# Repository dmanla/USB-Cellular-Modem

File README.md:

# USB-Cellular-Modem: NB-IoT/Cat-M Terminal

## Overview
**USB-Cellular-Modem** is an open-hardware cellular terminal designed for to enable any device equipped with USB to interface with LTE-CAT-M1 or NB-IOT Cellular Networks. The modem is low-power enough to be used as a back-up cellular interface for any mobile device. 

**NOTE:** Due to Apple restrictions on USB Interface access, this device cannot interface with Apple Devices. There may be a bluetooth variant in the future.

The core of the device is the **SIMCOM 7080G**, providing global NB-IoT and Cat-M1 connectivity with a focus on a minimal RF footprint and user-controlled privacy.

---

## Key Security & Design Features
* **Active-Discharge Kill Switch**: A physical SPDT slide switch ($SW1$) that disconnects the buck converter and actively shorts the $+BATT$ rail to ground through a $10\Omega$ resistor ($R4$). This ensures the $1000\mu F$ bulk capacitance is drained in milliseconds, preventing any residual "heartbeat" transmissions.
* **UART Signal Isolation**: $1k\Omega$ series resistors ($R8$, $R9$, $R10$, $R11$) are placed on all data lines (TX, RX, RTS, DTR). This prevents the **CH343P** from "back-powering" the modem via internal ESD diodes when the master power is cut.
* **Automated Power Trigger**: The **DTR** line is tied to a **DTC143Z** digital transistor ($Q1$). Opening the serial port on the host machine automatically pulses the modem's **PWRKEY**, initiating the boot sequence.
* **Local RF Shielding**: The PCB includes grounded rectangular frames designed for soldering a metal Faraday cage over the antenna matching network ($J1$, $C2$, $R1$, $C3$) to mitigate local signal sniffing.
* **eSIM Integration**: Includes a dedicated footprint for the **ST4SIM-200M** GSMA-certified eSIM for tamper-resistant credential storage.

---

### Included Hardware
| Component | Part Number | Description |
| :--- | :--- | :--- |
| **Cellular Module** | **SIMCOM 7080G** | Global NB-IoT / Cat-M1 with GNSS. |
| **USB-UART Bridge** | **WCH CH343P** | High-speed USB to serial converter. |
| **Power Regulator** | **TPS62A01ADRL** | 1000mA Synchronous Buck Converter (5V to 3.8V). |
| **Embedded SIM** | **ST4SIM-200M** | Industrial-grade MFF2 eSIM. |
| **Nano SIM Slot** | **CUI Hinged NSIM-2** | Nano-SIM Card Slot. |

---

## Technical Specifications
* **Input Power**: USB VBUS (+5V, 500mA).
* **Logic Level**: $1.8V$ Internal ($VDD\_EXT$), isolated from $3.3V$ USB signals.
* **Stackup**: 4-Layer PCB with solid internal ground planes.
* **EDA Software**: **KiCad 9.0.7**.

## Usage
1.  **Enable Device**: Flip $SW1$ to the `ON` position.
2.  **Communication**: Open a serial terminal (e.g., `minicom` or `screen`) at `115200` baud. The DTR toggle will boot the modem.
3.  **Kill Session**: Flip $SW1$ to the `OFF` position. The modem is physically disconnected and the power rail is grounded.

---

## Front 3D Render

## Back 3D Render

## License

Dimensions and Modem Placement Derived from [techstudio-design/sim7080_dev_board](https://github.com/techstudio-design/sim7080_dev_board)

All PCB design files and hardware are released under the [Creative Commons Attribution Share Alike 4.0](https://choosealicense.com/licenses/cc-by-sa-4.0/) license.

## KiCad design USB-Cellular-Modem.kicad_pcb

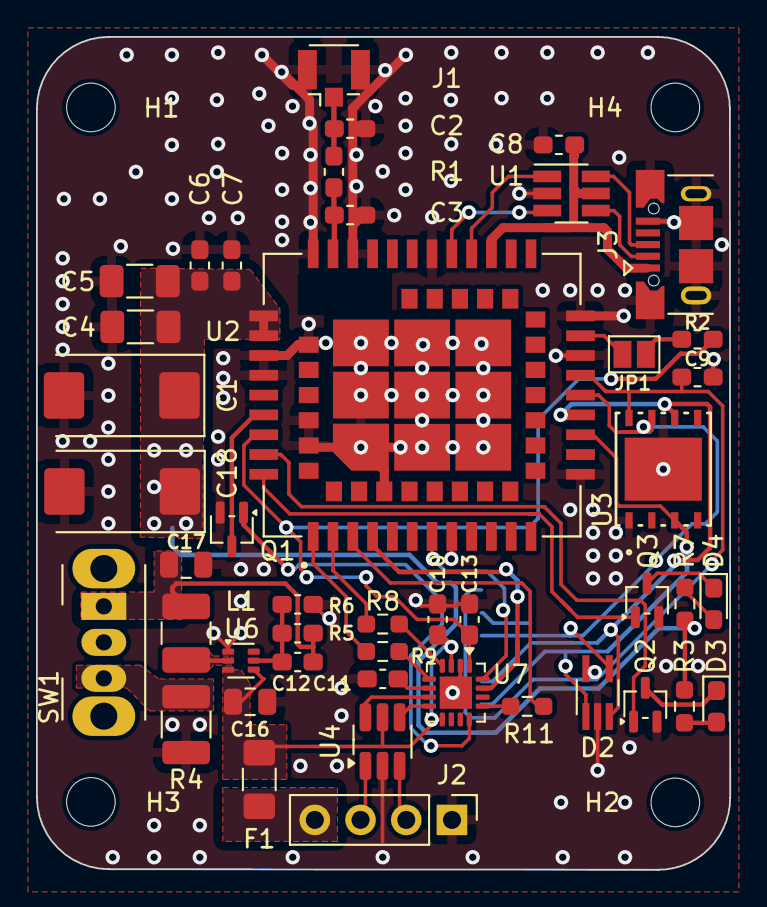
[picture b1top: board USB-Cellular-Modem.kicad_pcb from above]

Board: 4 copper layers, 38.5 x 46.3 mm, 50 parts (1 on the bottom side), 43 nets.

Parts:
C1, C18: 500uF; CP_EIA-7343-30_AVX-N_HandSolder
C2, C3: NC; C_0603_1608Metric_Pad1.05x0.95mm_HandSolder
C4, C5: 100uF; C_1206_3216Metric_Pad1.33x1.80mm_HandSolder
C6: 1uF; C_0603_1608Metric_Pad1.05x0.95mm_HandSolder
C7, C8, C9: 0.1uF; C_0603_1608Metric_Pad1.05x0.95mm_HandSolder
C10, C13: 1uF; C_0603_1608Metric_Pad1.08x0.95mm_HandSolder
C11: 100nF; C_0603_1608Metric_Pad1.08x0.95mm_HandSolder
C12: 120pF; C_0603_1608Metric_Pad1.08x0.95mm_HandSolder
C16: 10uF; C_0805_2012Metric
C17: 22uF; C_0805_2012Metric
D2: ESDA6V1W5; SOT-353_SC-70-5_Handsoldering
D3: NETLIGHT; LED_0603_1608Metric_Pad1.05x0.95mm_HandSolder
D4: STATUS; LED_0603_1608Metric_Pad1.05x0.95mm_HandSolder
F1: PTC_FUSE; Fuse_1206_3216Metric_Pad1.42x1.75mm_HandSolder
H1, H2, H3, H4: MountingHole_Pad; MountingHole_2.7mm_M2.5
J1: LTE Antenna; U.FL_Hirose_U.FL-R-SMT-1_Vertical
J2: USB_JUMPER; PinHeader_1x04_P2.54mm_Vertical
J3: USB_B_Micro; USB_Micro-B_XKB_U254-051T-4BH83-F1S
J4: SIM_Card; nanoSIM_Hinged_CUI_NSIM-2-C
JP1: SolderJumper_2_Open; SolderJumper-2_P1.3mm_Open_Pad1.0x1.5mm
L1: 1uH; L_1210_3225Metric_Pad1.42x2.65mm_HandSolder
Q1: DTC143Z; SOT-323_SC-70
Q2, Q3: DTC143ZU; SOT-323_SC-70
R1: 0; R_0603_1608Metric_Pad1.05x0.95mm_HandSolder
R2: 10k; R_0603_1608Metric_Pad1.05x0.95mm_HandSolder
R3, R7, R8, R9, R11: 1k; R_0603_1608Metric_Pad0.98x0.95mm_HandSolder
R4: 10R; R_1210_3225Metric_Pad1.30x2.65mm_HandSolder
R5: 536k; C_0603_1608Metric_Pad1.08x0.95mm_HandSolder
R6: 100k; C_0603_1608Metric_Pad1.08x0.95mm_HandSolder
SW1: KILL_SWITCH; SW_Slide_SPDT_Angled_CK_OS102011MA1Q
U1, U4: USBLC6-2SC6; SOT-23-6_Handsoldering
U2: SIM7080G
U3: ST4SIM-200M
U6: TPS62A01ADRL; SOT-563
U7: CH343P; WCH_QFN-16-1EP_3x3mm_P0.5mm_EP1.8x1.8mm

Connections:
+1V8: C13.1, R2.1, U2.40 (VDD_EXT), U7.1 (VIO)
+5V: C10.1, C16.1, F1.2, U4.5 (VBUS), U6.3 (VIN), U6.4 (EN), U7.3 (VDD5), U7.9 (VBUS)
+BATT: C1.1, C4.1, C5.1, C6.1, C7.1, C18.1, R3.1, R7.1, SW1.2 (B), U2.34 (VBAT), U2.35 (VBAT)
/SIM7080_Interface/PWR_SIGNAL: Q1.3 (C), U2.39 (PWRKEY)
/SIM7080_Interface/UART_RXD: R9.2, U2.1 (UART1_TXD)
/SIM7080_Interface/UART_TXD: R8.2, U2.2 (UART1_RXD)
/SIM7080_Interface/UART_~CTS: U2.4 (UART1_CTS), U7.15 (~CTS)
/SIM7080_Interface/UART_~RI: U2.7 (UART1_RI), U7.16 (~RI)
/SIM7080_Interface/UART_~RTS: R11.2, U2.3 (UART1_RTS)
/SIM7080_module/DEBUG_VBUS: C8.1, J3.1 (VBUS), U1.5 (VBUS), U2.24 (USB_VBUS)
/SIM7080_module/NET_LED_CTRL: Q2.1 (B), U2.41 (NETLIGHT)
/SIM7080_module/STATUS_LED_CTRL: Q3.1 (B), U2.42 (STATUS)
GND: C1.2, C2.2, C3.2, C4.2, C5.2, C6.2, C7.2, C8.2, C9.2, C10.2, C11.2, C13.2, C16.2, C17.2, C18.2, D2.2 (A), J1.2 (Ext), J2.1, J3.5 (GND), J3.6 (Shield), J4.5 (GND), Q1.2 (E), Q2.2 (E), Q3.2 (E), R4.2, R6.2, U1.2 (GND), U2.8 (GND), U2.13 (GND), U2.19 (GND), U2.21 (GND), U2.27 (GND), U2.30 (GND), U2.31 (GND), U2.33 (GND), U2.36 (GND), U2.37 (GND), U2.45 (GND), U2.63 (GND), U2.66 (GND), U2.67 (GND), U2.69 (GND), U2.70 (GND), U2.71 (GND), U2.72 (GND), U2.73 (GND), U2.74 (GND), U2.75 (GND), U2.76 (GND), U2.77 (GND), U3.1 (GND), U3.9, U4.2 (GND), U6.1 (GND), U7.2 (GND), U7.17 (GND_EPAD)
unnamed: D3.2 (A), R3.2
unnamed: D3.1 (K), Q2.3 (C)
unnamed: D4.2 (A), R7.2
unnamed: D4.1 (K), Q3.3 (C)
unnamed: C2.1, J1.1 (In), R1.2
unnamed: J2.2, U4.3 (IO2)
unnamed: J2.3, U4.1 (IO1)
unnamed: J3.3 (D+), U1.6 (IO1)
unnamed: J3.2 (D-), U1.4 (IO2)
unnamed: D2.3 (K), J4.3 (CLK), U2.16 (SIM_CLK), U3.6 (CLK)
unnamed: D2.1 (K), J4.7 (I/O), U2.15 (SIM_DATA), U3.3 (I/O)
unnamed: D2.4 (K), J4.2 (RST), U2.17 (SIM_RST), U3.7 (RESET)
unnamed: C9.1, D2.5 (K), J4.1 (VCC), U2.18 (SIM_VDD), U3.8 (VCC)
unnamed: JP1.1 (A), U2.20 (BOOT_CFG)
unnamed: JP1.2 (B), R2.2
unnamed: Q1.1 (B), U7.12 (~DTR)
unnamed: C12.1, C17.1, L1.2, R5.1, SW1.1 (A)
unnamed: R4.1, SW1.3 (C)
unnamed: C3.1, R1.1, U2.32 (RF_ANT)
unnamed: U1.3 (IO2), U2.26 (USB_DM)
unnamed: U1.1 (IO1), U2.25 (USB_DP)
unnamed: C12.2, R5.2, R6.1, U6.5 (FB)
unnamed: L1.1, U6.2 (SW)
unnamed: R9.1, U7.5 (RXD)
unnamed: R8.1, U7.4 (TXD)
unnamed: U4.6 (IO1), U7.7 (UD+)
unnamed: U4.4 (IO2), U7.8 (UD-)
unnamed: C11.1, U7.6 (V3_{OUT})
unnamed: R11.1, U7.13 (~RTS)
VBUS: F1.1, J2.4

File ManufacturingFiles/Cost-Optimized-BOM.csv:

Reference,Qty,Value/Description,Manufacturer,Part Number,Distributor,Unit Price (10 Qty),Total (10 Qty)
U2,1,Cellular Module Cat-M/NB-IoT,SimCom,SIM7080G,LCSC (C2943992),$10.86,$108.60
U3,1,eSIM IC GSMA,STMicroelectronics,ST4SIM-200M,Mouser / ST,$3.00,$30.00
U7,1,USB to UART Bridge,WCH,CH343P,LCSC (C2846043),$1.03,$10.30
U6,1,Buck Converter 1A,Texas Instruments,TPS62A01ADRLR,DigiKey / Mouser,$0.13,$1.30
"U1,U4",2,ESD Protection 2-Line,Yenji Elec,USBLC6-2SC6,LCSC (C323793),$0.07,$1.40
D2,1,TVS Diode Array 5-Line,STMicroelectronics,ESDA6V1W5,LCSC (C48677),$0.10,$1.00
"C1,C18",2,470uF 6.3V Tantalum Case D,Kyocera AVX,TAJD477K006RNJ,LCSC (C7229),$0.86,$17.20
J1,1,U.FL Connector (SMT),Hirose (HRS),U.FL-R-SMT-1(80),LCSC (C88374),$0.13,$1.30
J3,1,USB Micro-B Connector,Shou Han,Micro-USB-5P,LCSC (C10418),$0.04,$0.40
J4,1,Nano SIM Connector Hinged,Shou Han,NANO SIM 7P H1.37,LCSC (C7529384),$0.27,$2.70
SW1,1,Slide Switch SPDT,XKB Connectivity,SS-12D10-G5,LCSC (C394953),$0.03,$0.30
F1,1,PTC Fuse 1.1A 1206,SART,SMD1206-110-16V,LCSC (C20537),$0.04,$0.40
L1,1,Inductor 1uH 1A 1210,Sunlord,SWPA3015S1R0MT,LCSC (C1046),$0.05,$0.50
"Q1,Q2,Q3",3,Digital Transistor NPN,Changjiang,DTC143ZUA,LCSC (C151046),$0.02,$0.60
D3,1,LED Blue 0603,Hubei Kento,19-217/BHC-ZL1M2RY/3T,LCSC (C2293),$0.02,$0.20
D4,1,LED Red 0603,Hubei Kento,17-21/R6C-AP1Q2L/3T,LCSC (C2290),$0.02,$0.20
"C4,C5",2,100uF 6.3V X5R 1206,Samsung,CL31A107MQHNNNE,LCSC (C14863),$0.14,$2.80
C17,1,22uF 10V X5R 0805,Samsung,CL21A226MPQNNNE,LCSC (C15652),$0.03,$0.30
C16,1,10uF 10V X5R 0805,Samsung,CL21A106KPCLQNC,LCSC (C15783),$0.01,$0.10
"C6,C10,C13",3,1uF 16V X7R 0603,Samsung,CL10B105KO8NNNC,LCSC (C15849),$0.00,$0.12
C11,1,100nF 16V X7R 0603,Samsung,CL10B104KB8NNNC,LCSC (C1525),$0.00,$0.03
"C7,C8,C9",3,100nF 16V X7R 0603,Samsung,CL10B104KB8NNNC,LCSC (C1525),$0.00,$0.09
C12,1,120pF 50V C0G 0603,Samsung,CL10C121JB8NNNC,LCSC (C1548),$0.00,$0.03
R6,1,100k 1% 0603,Uni-Royal,0603WAF1003T5E,LCSC (C25804),$0.00,$0.02
R5,1,536k 1% 0603,Uni-Royal,0603WAF5363T5E,LCSC (C23187),$0.00,$0.02
R2,1,10k 1% 0603,Uni-Royal,0603WAF1002T5E,LCSC (C25744),$0.00,$0.02
"R3,R7,R8,R9,R11",5,1k 1% 0603,Uni-Royal,0603WAF1001T5E,LCSC (C25741),$0.00,$0.10
R4,1,10R 1% 1210,Uni-Royal,1210WAF100JT5E,LCSC (C17918),$0.01,$0.10
R1,1,0R Jumper 0603,Uni-Royal,0603WAF0000T5E,LCSC (C21189),$0.00,$0.02
JP1,1,Solder Jumper Open,N/A,N/A,N/A,$0.00,$0.00
J2,1,Pin Header 1x04,Generic,2.54mm-1x4P,LCSC (C124375),$0.01,$0.10
H1-H4,4,Mounting Hole M2.5,N/A,N/A,N/A,$0.00,$0.00
"C2,C3",2,DNP,N/A,N/A,N/A,$0.00,$0.00
,,,,,,,
,,,,,,Total Unit Cost (Qty: 10),$18.03

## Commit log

2026-02-08 AI Readme
2026-02-08 add BOM in different formats
2026-02-08 AI Generated Cost Optimized BOM's

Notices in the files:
USB-Cellular-Modem.kicad_pcb:
Copyright: Tech Studio Design, 2021
